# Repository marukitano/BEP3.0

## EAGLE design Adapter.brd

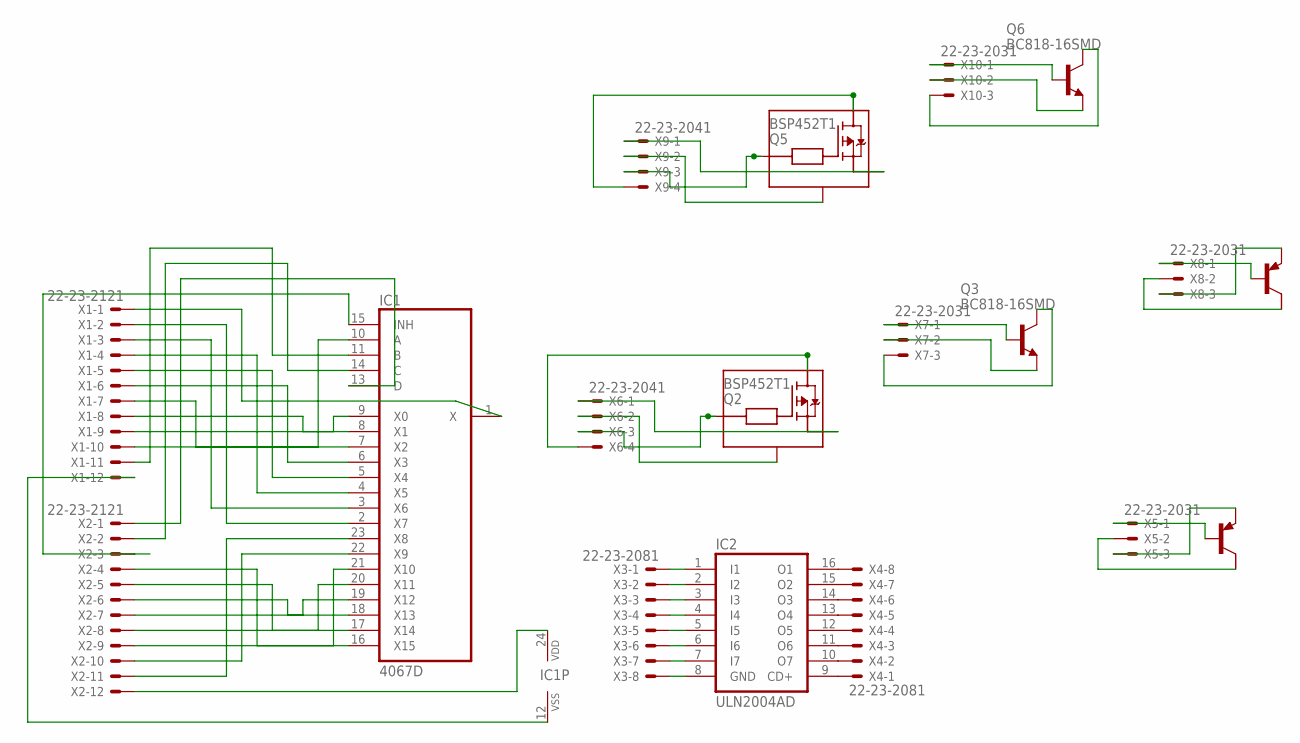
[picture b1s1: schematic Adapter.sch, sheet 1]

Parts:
IC1: 4067D; SO24W
IC2: ULN2004AD; SO16
Q1, Q4: BCP53T1; SOT223
Q2, Q5: BSP452T1; SOT223
Q3, Q6: BC818-16SMD; SOT23-BEC
X1, X2: 22-23-2121
X3, X4: 22-23-2081
X5, X7, X8, X10: 22-23-2031
X6, X9: 22-23-2041

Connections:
unnamed: IC1.2 (X7), X1.2
unnamed: IC1.1 (X), X1.1
unnamed: IC1.3 (X6), X1.3
unnamed: IC1.4 (X5), X1.4
unnamed: IC1.5 (X4), X1.5
unnamed: IC1.6 (X3), X1.6
unnamed: IC1.7 (X2), X1.7
unnamed: IC1.8 (X1), X1.8
unnamed: IC1.9 (X0), X1.9
unnamed: IC1.10 (A), X1.10
unnamed: IC1.11 (B), X1.11
unnamed: IC1.16 (X15), X2.4
unnamed: IC1.17 (X14), X2.5
unnamed: IC1.18 (X13), X2.6
unnamed: IC1.19 (X12), X2.7
unnamed: IC1.20 (X11), X2.8
unnamed: IC1.21 (X10), X2.9
unnamed: IC1.22 (X9), X2.10
unnamed: IC1.23 (X8), X2.11
unnamed: IC1.12 (VSS), X1.12
unnamed: IC1.24 (VDD), X2.12
unnamed: IC1.15 (INH), X2.3
unnamed: IC1.14 (C), X2.2
unnamed: IC1.13 (D), X2.1
unnamed: IC2.1 (I1), X3.1
unnamed: IC2.2 (I2), X3.2
unnamed: IC2.3 (I3), X3.3
unnamed: IC2.4 (I4), X3.4
unnamed: IC2.5 (I5), X3.5
unnamed: IC2.6 (I6), X3.6
unnamed: IC2.7 (I7), X3.7
unnamed: IC2.8 (GND), X3.8
unnamed: IC2.9 (CD+), X4.1
unnamed: IC2.10 (O7), X4.2
unnamed: IC2.11 (O6), X4.3
unnamed: IC2.12 (O5), X4.4
unnamed: IC2.13 (O4), X4.5
unnamed: IC2.14 (O3), X4.6
unnamed: IC2.15 (O2), X4.7
unnamed: IC2.16 (O1), X4.8
unnamed: Q1.1 (B), X5.1
unnamed: Q1.3 (E), X5.3
unnamed: Q1.2 (C), X5.2
unnamed: Q2.1 (OUT), X6.1
unnamed: Q2.2 (GND), X6.2
unnamed: Q2.3 (IN), X6.3
unnamed: Q2.4 (V+), X6.4
unnamed: Q3.B, X7.1
unnamed: Q3.E, X7.2
unnamed: Q3.C, X7.3
unnamed: Q4.1 (B), X8.1
unnamed: Q4.2 (C), X8.2
unnamed: Q4.3 (E), X8.3
unnamed: Q5.1 (OUT), X9.1
unnamed: Q5.2 (GND), X9.2
unnamed: Q5.3 (IN), X9.3
unnamed: Q5.4 (V+), X9.4
unnamed: Q6.B, X10.1
unnamed: Q6.E, X10.2
unnamed: Q6.C, X10.3

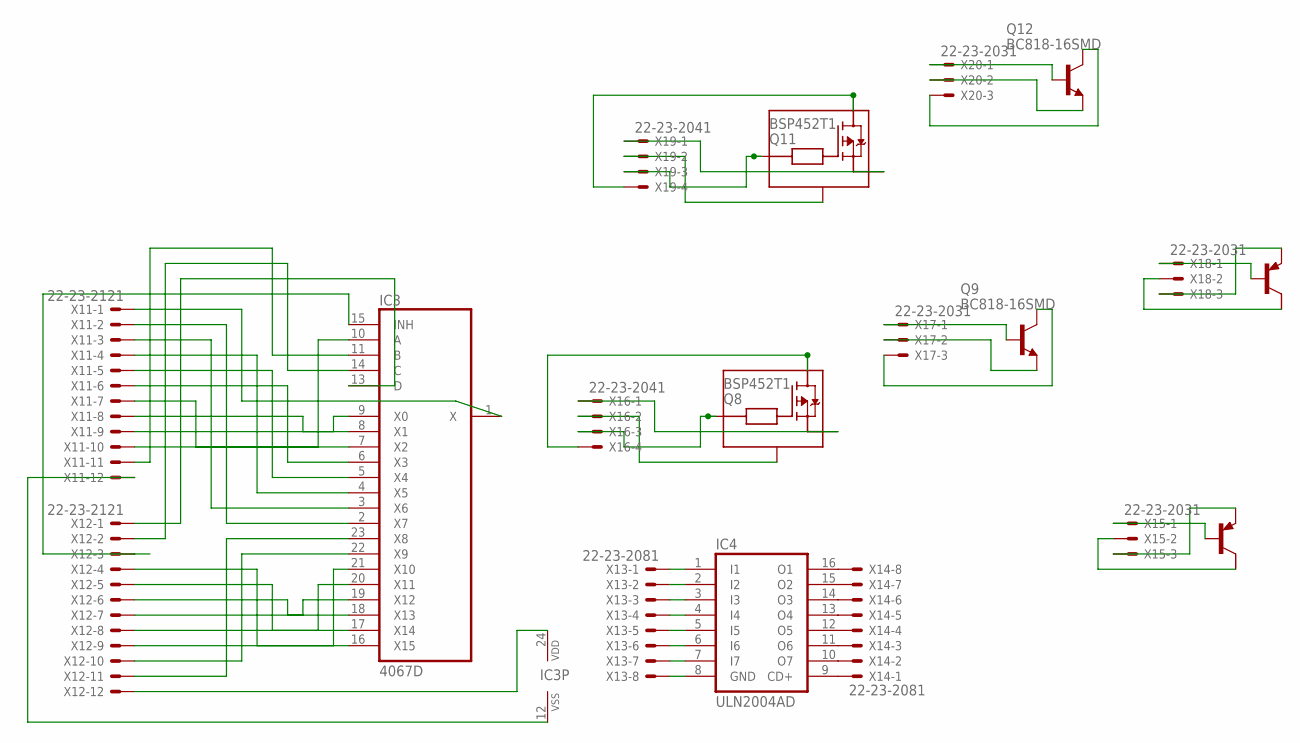
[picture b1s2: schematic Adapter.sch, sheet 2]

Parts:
IC3: 4067D; SO24W
IC4: ULN2004AD; SO16
Q7, Q10: BCP53T1; SOT223
Q8, Q11: BSP452T1; SOT223
Q9, Q12: BC818-16SMD; SOT23-BEC
X11, X12: 22-23-2121
X13, X14: 22-23-2081
X15, X17, X18, X20: 22-23-2031
X16, X19: 22-23-2041

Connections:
unnamed: IC3.2 (X7), X11.2
unnamed: IC3.1 (X), X11.1
unnamed: IC3.3 (X6), X11.3
unnamed: IC3.4 (X5), X11.4
unnamed: IC3.5 (X4), X11.5
unnamed: IC3.6 (X3), X11.6
unnamed: IC3.7 (X2), X11.7
unnamed: IC3.8 (X1), X11.8
unnamed: IC3.9 (X0), X11.9
unnamed: IC3.10 (A), X11.10
unnamed: IC3.11 (B), X11.11
unnamed: IC3.16 (X15), X12.4
unnamed: IC3.17 (X14), X12.5
unnamed: IC3.18 (X13), X12.6
unnamed: IC3.19 (X12), X12.7
unnamed: IC3.20 (X11), X12.8
unnamed: IC3.21 (X10), X12.9
unnamed: IC3.22 (X9), X12.10
unnamed: IC3.23 (X8), X12.11
unnamed: IC3.12 (VSS), X11.12
unnamed: IC3.24 (VDD), X12.12
unnamed: IC3.15 (INH), X12.3
unnamed: IC3.14 (C), X12.2
unnamed: IC3.13 (D), X12.1
unnamed: IC4.1 (I1), X13.1
unnamed: IC4.2 (I2), X13.2
unnamed: IC4.3 (I3), X13.3
unnamed: IC4.4 (I4), X13.4
unnamed: IC4.5 (I5), X13.5
unnamed: IC4.6 (I6), X13.6
unnamed: IC4.7 (I7), X13.7
unnamed: IC4.8 (GND), X13.8
unnamed: IC4.9 (CD+), X14.1
unnamed: IC4.10 (O7), X14.2
unnamed: IC4.11 (O6), X14.3
unnamed: IC4.12 (O5), X14.4
unnamed: IC4.13 (O4), X14.5
unnamed: IC4.14 (O3), X14.6
unnamed: IC4.15 (O2), X14.7
unnamed: IC4.16 (O1), X14.8
unnamed: Q7.1 (B), X15.1
unnamed: Q7.2 (C), X15.2
unnamed: Q7.3 (E), X15.3
unnamed: Q8.1 (OUT), X16.1
unnamed: Q8.2 (GND), X16.2
unnamed: Q8.3 (IN), X16.3
unnamed: Q8.4 (V+), X16.4
unnamed: Q9.B, X17.1
unnamed: Q9.E, X17.2
unnamed: Q9.C, X17.3
unnamed: Q10.1 (B), X18.1
unnamed: Q10.2 (C), X18.2
unnamed: Q10.3 (E), X18.3
unnamed: Q11.1 (OUT), X19.1
unnamed: Q11.2 (GND), X19.2
unnamed: Q11.3 (IN), X19.3
unnamed: Q11.4 (V+), X19.4
unnamed: Q12.B, X20.1
unnamed: Q12.E, X20.2
unnamed: Q12.C, X20.3

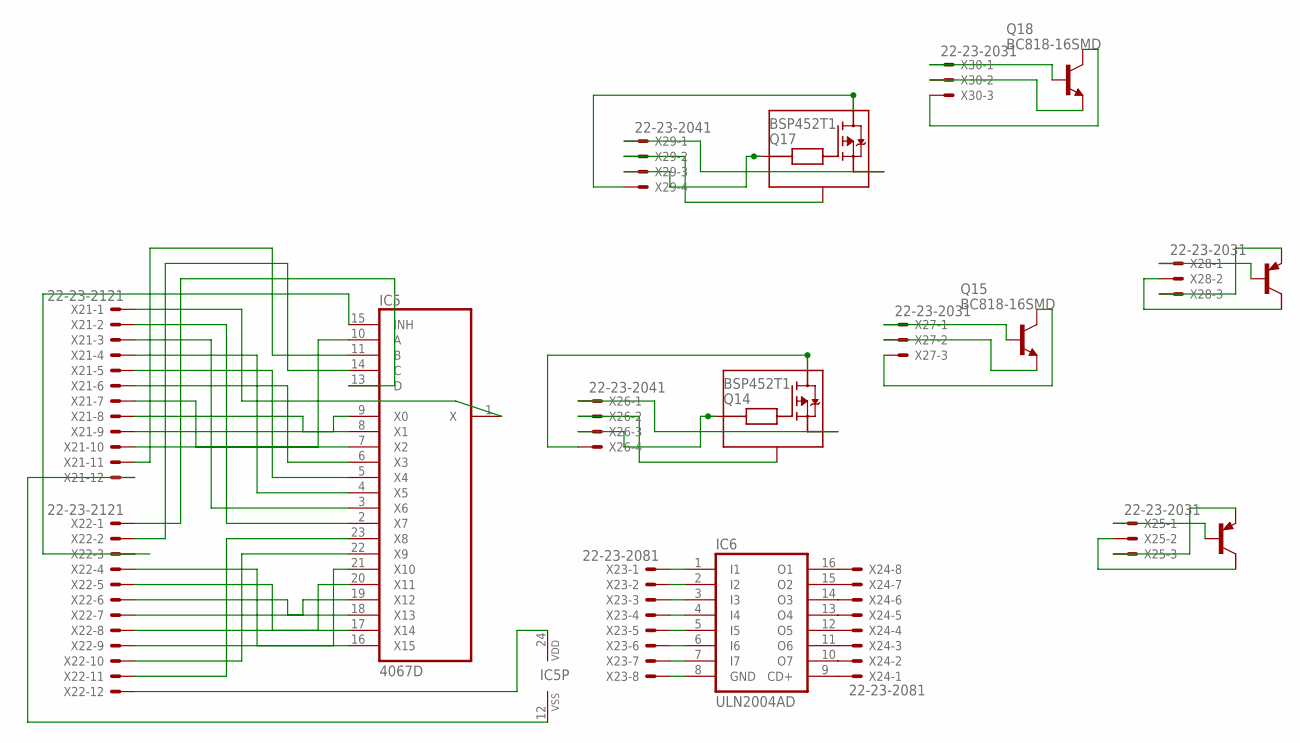
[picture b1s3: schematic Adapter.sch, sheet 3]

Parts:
IC5: 4067D; SO24W
IC6: ULN2004AD; SO16
Q13, Q16: BCP53T1; SOT223
Q14, Q17: BSP452T1; SOT223
Q15, Q18: BC818-16SMD; SOT23-BEC
X21, X22: 22-23-2121
X23, X24: 22-23-2081
X25, X27, X28, X30: 22-23-2031
X26, X29: 22-23-2041

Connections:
unnamed: IC5.2 (X7), X21.2
unnamed: IC5.1 (X), X21.1
unnamed: IC5.3 (X6), X21.3
unnamed: IC5.4 (X5), X21.4
unnamed: IC5.5 (X4), X21.5
unnamed: IC5.6 (X3), X21.6
unnamed: IC5.7 (X2), X21.7
unnamed: IC5.8 (X1), X21.8
unnamed: IC5.9 (X0), X21.9
unnamed: IC5.10 (A), X21.10
unnamed: IC5.11 (B), X21.11
unnamed: IC5.16 (X15), X22.4
unnamed: IC5.17 (X14), X22.5
unnamed: IC5.18 (X13), X22.6
unnamed: IC5.19 (X12), X22.7
unnamed: IC5.20 (X11), X22.8
unnamed: IC5.21 (X10), X22.9
unnamed: IC5.22 (X9), X22.10
unnamed: IC5.23 (X8), X22.11
unnamed: IC5.12 (VSS), X21.12
unnamed: IC5.24 (VDD), X22.12
unnamed: IC5.15 (INH), X22.3
unnamed: IC5.14 (C), X22.2
unnamed: IC5.13 (D), X22.1
unnamed: IC6.1 (I1), X23.1
unnamed: IC6.2 (I2), X23.2
unnamed: IC6.3 (I3), X23.3
unnamed: IC6.4 (I4), X23.4
unnamed: IC6.5 (I5), X23.5
unnamed: IC6.6 (I6), X23.6
unnamed: IC6.7 (I7), X23.7
unnamed: IC6.8 (GND), X23.8
unnamed: IC6.9 (CD+), X24.1
unnamed: IC6.10 (O7), X24.2
unnamed: IC6.11 (O6), X24.3
unnamed: IC6.12 (O5), X24.4
unnamed: IC6.13 (O4), X24.5
unnamed: IC6.14 (O3), X24.6
unnamed: IC6.15 (O2), X24.7
unnamed: IC6.16 (O1), X24.8
unnamed: Q13.1 (B), X25.1
unnamed: Q13.2 (C), X25.2
unnamed: Q13.3 (E), X25.3
unnamed: Q14.1 (OUT), X26.1
unnamed: Q14.2 (GND), X26.2
unnamed: Q14.3 (IN), X26.3
unnamed: Q14.4 (V+), X26.4
unnamed: Q15.B, X27.1
unnamed: Q15.E, X27.2
unnamed: Q15.C, X27.3
unnamed: Q16.1 (B), X28.1
unnamed: Q16.2 (C), X28.2
unnamed: Q16.3 (E), X28.3
unnamed: Q17.1 (OUT), X29.1
unnamed: Q17.2 (GND), X29.2
unnamed: Q17.3 (IN), X29.3
unnamed: Q17.4 (V+), X29.4
unnamed: Q18.B, X30.1
unnamed: Q18.E, X30.2
unnamed: Q18.C, X30.3

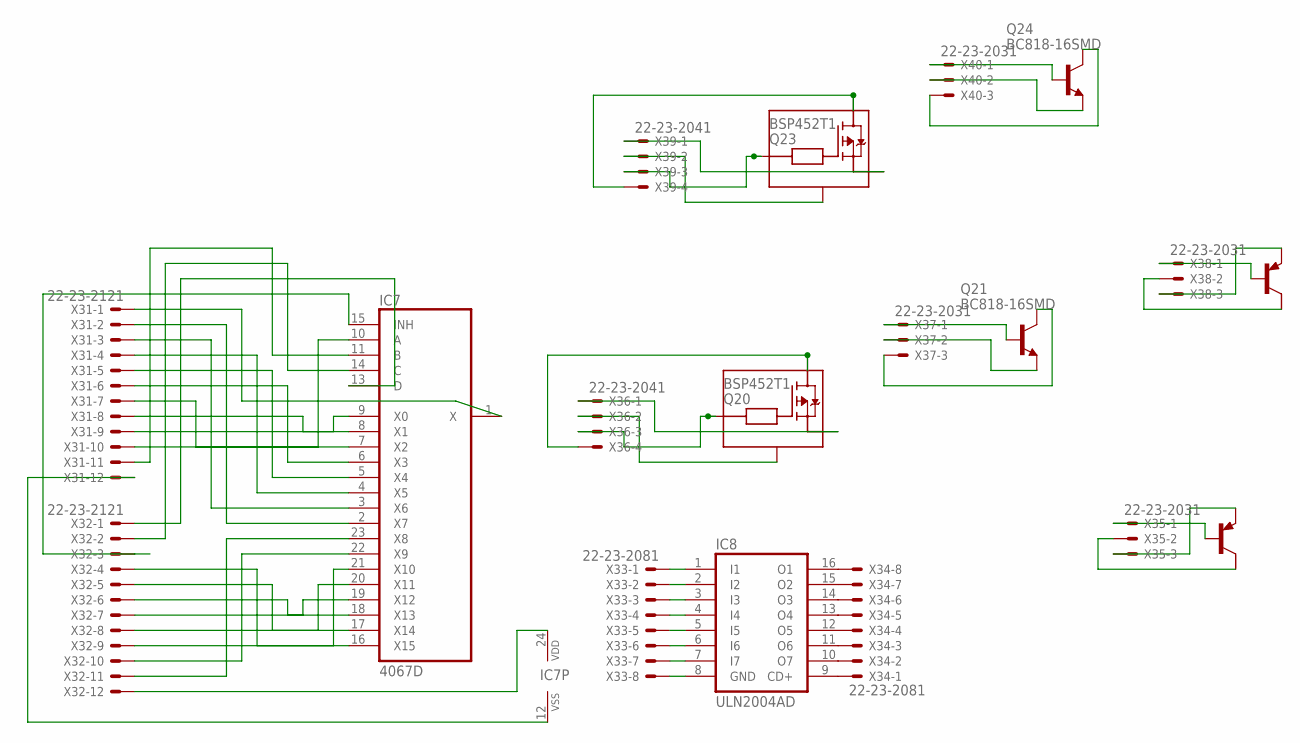
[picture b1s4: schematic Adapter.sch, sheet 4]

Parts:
IC7: 4067D; SO24W
IC8: ULN2004AD; SO16
Q19, Q22: BCP53T1; SOT223
Q20, Q23: BSP452T1; SOT223
Q21, Q24: BC818-16SMD; SOT23-BEC
X31, X32: 22-23-2121
X33, X34: 22-23-2081
X35, X37, X38, X40: 22-23-2031
X36, X39: 22-23-2041

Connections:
unnamed: IC7.2 (X7), X31.2
unnamed: IC7.1 (X), X31.1
unnamed: IC7.3 (X6), X31.3
unnamed: IC7.4 (X5), X31.4
unnamed: IC7.5 (X4), X31.5
unnamed: IC7.6 (X3), X31.6
unnamed: IC7.7 (X2), X31.7
unnamed: IC7.8 (X1), X31.8
unnamed: IC7.9 (X0), X31.9
unnamed: IC7.10 (A), X31.10
unnamed: IC7.11 (B), X31.11
unnamed: IC7.16 (X15), X32.4
unnamed: IC7.17 (X14), X32.5
unnamed: IC7.18 (X13), X32.6
unnamed: IC7.19 (X12), X32.7
unnamed: IC7.20 (X11), X32.8
unnamed: IC7.21 (X10), X32.9
unnamed: IC7.22 (X9), X32.10
unnamed: IC7.23 (X8), X32.11
unnamed: IC7.12 (VSS), X31.12
unnamed: IC7.24 (VDD), X32.12
unnamed: IC7.15 (INH), X32.3
unnamed: IC7.14 (C), X32.2
unnamed: IC7.13 (D), X32.1
unnamed: IC8.1 (I1), X33.1
unnamed: IC8.2 (I2), X33.2
unnamed: IC8.3 (I3), X33.3
unnamed: IC8.4 (I4), X33.4
unnamed: IC8.5 (I5), X33.5
unnamed: IC8.6 (I6), X33.6
unnamed: IC8.7 (I7), X33.7
unnamed: IC8.8 (GND), X33.8
unnamed: IC8.9 (CD+), X34.1
unnamed: IC8.10 (O7), X34.2
unnamed: IC8.11 (O6), X34.3
unnamed: IC8.12 (O5), X34.4
unnamed: IC8.13 (O4), X34.5
unnamed: IC8.14 (O3), X34.6
unnamed: IC8.15 (O2), X34.7
unnamed: IC8.16 (O1), X34.8
unnamed: Q19.1 (B), X35.1
unnamed: Q19.2 (C), X35.2
unnamed: Q19.3 (E), X35.3
unnamed: Q20.1 (OUT), X36.1
unnamed: Q20.2 (GND), X36.2
unnamed: Q20.3 (IN), X36.3
unnamed: Q20.4 (V+), X36.4
unnamed: Q21.B, X37.1
unnamed: Q21.E, X37.2
unnamed: Q21.C, X37.3
unnamed: Q22.1 (B), X38.1
unnamed: Q22.2 (C), X38.2
unnamed: Q22.3 (E), X38.3
unnamed: Q23.1 (OUT), X39.1
unnamed: Q23.2 (GND), X39.2
unnamed: Q23.3 (IN), X39.3
unnamed: Q23.4 (V+), X39.4
unnamed: Q24.B, X40.1
unnamed: Q24.E, X40.2
unnamed: Q24.C, X40.3

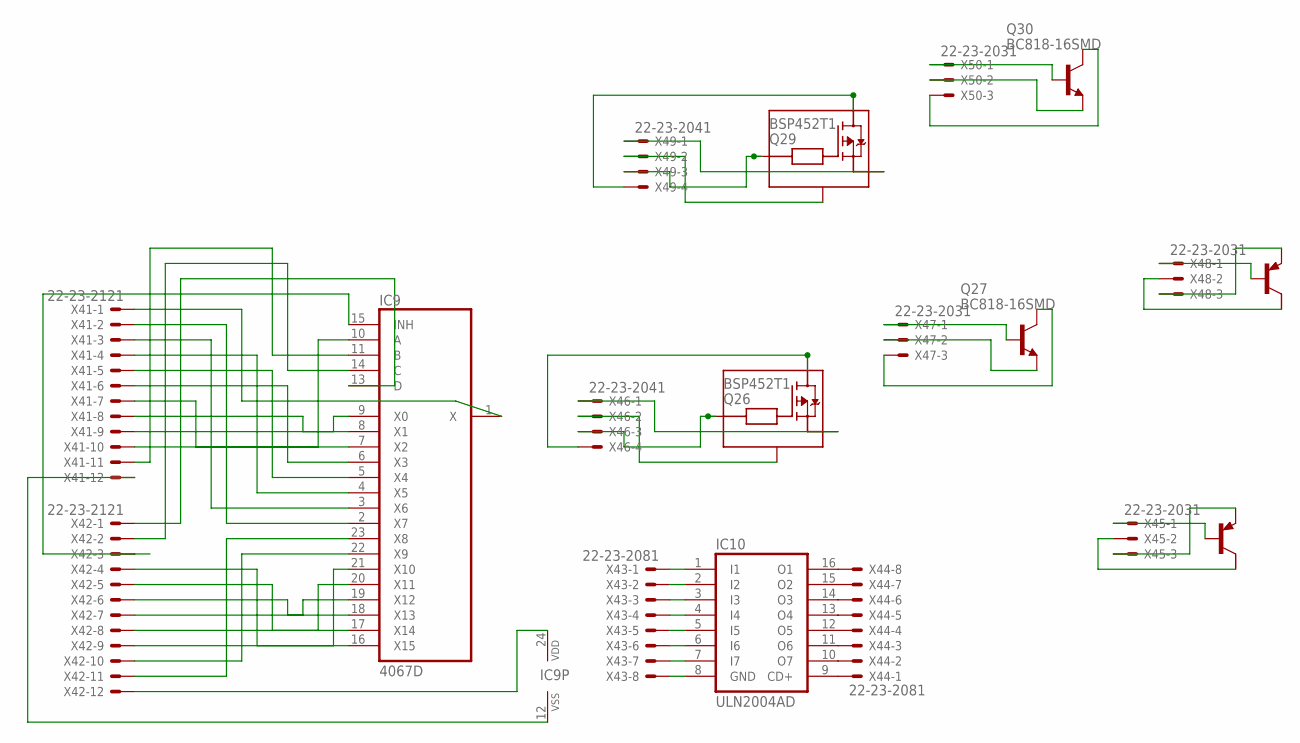
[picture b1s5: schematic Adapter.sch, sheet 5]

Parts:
IC9: 4067D; SO24W
IC10: ULN2004AD; SO16
Q25, Q28: BCP53T1; SOT223
Q26, Q29: BSP452T1; SOT223
Q27, Q30: BC818-16SMD; SOT23-BEC
X41, X42: 22-23-2121
X43, X44: 22-23-2081
X45, X47, X48, X50: 22-23-2031
X46, X49: 22-23-2041

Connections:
unnamed: IC9.2 (X7), X41.2
unnamed: IC9.1 (X), X41.1
unnamed: IC9.3 (X6), X41.3
unnamed: IC9.4 (X5), X41.4
unnamed: IC9.5 (X4), X41.5
unnamed: IC9.6 (X3), X41.6
unnamed: IC9.7 (X2), X41.7
unnamed: IC9.8 (X1), X41.8
unnamed: IC9.9 (X0), X41.9
unnamed: IC9.10 (A), X41.10
unnamed: IC9.11 (B), X41.11
unnamed: IC9.16 (X15), X42.4
unnamed: IC9.17 (X14), X42.5
unnamed: IC9.18 (X13), X42.6
unnamed: IC9.19 (X12), X42.7
unnamed: IC9.20 (X11), X42.8
unnamed: IC9.21 (X10), X42.9
unnamed: IC9.22 (X9), X42.10
unnamed: IC9.23 (X8), X42.11
unnamed: IC9.12 (VSS), X41.12
unnamed: IC9.24 (VDD), X42.12
unnamed: IC9.15 (INH), X42.3
unnamed: IC9.14 (C), X42.2
unnamed: IC9.13 (D), X42.1
unnamed: IC10.1 (I1), X43.1
unnamed: IC10.2 (I2), X43.2
unnamed: IC10.3 (I3), X43.3
unnamed: IC10.4 (I4), X43.4
unnamed: IC10.5 (I5), X43.5
unnamed: IC10.6 (I6), X43.6
unnamed: IC10.7 (I7), X43.7
unnamed: IC10.8 (GND), X43.8
unnamed: IC10.9 (CD+), X44.1
unnamed: IC10.10 (O7), X44.2
unnamed: IC10.11 (O6), X44.3
unnamed: IC10.12 (O5), X44.4
unnamed: IC10.13 (O4), X44.5
unnamed: IC10.14 (O3), X44.6
unnamed: IC10.15 (O2), X44.7
unnamed: IC10.16 (O1), X44.8
unnamed: Q25.1 (B), X45.1
unnamed: Q25.2 (C), X45.2
unnamed: Q25.3 (E), X45.3
unnamed: Q26.1 (OUT), X46.1
unnamed: Q26.2 (GND), X46.2
unnamed: Q26.3 (IN), X46.3
unnamed: Q26.4 (V+), X46.4
unnamed: Q27.B, X47.1
unnamed: Q27.E, X47.2
unnamed: Q27.C, X47.3
unnamed: Q28.1 (B), X48.1
unnamed: Q28.2 (C), X48.2
unnamed: Q28.3 (E), X48.3
unnamed: Q29.1 (OUT), X49.1
unnamed: Q29.2 (GND), X49.2
unnamed: Q29.3 (IN), X49.3
unnamed: Q29.4 (V+), X49.4
unnamed: Q30.B, X50.1
unnamed: Q30.E, X50.2
unnamed: Q30.C, X50.3

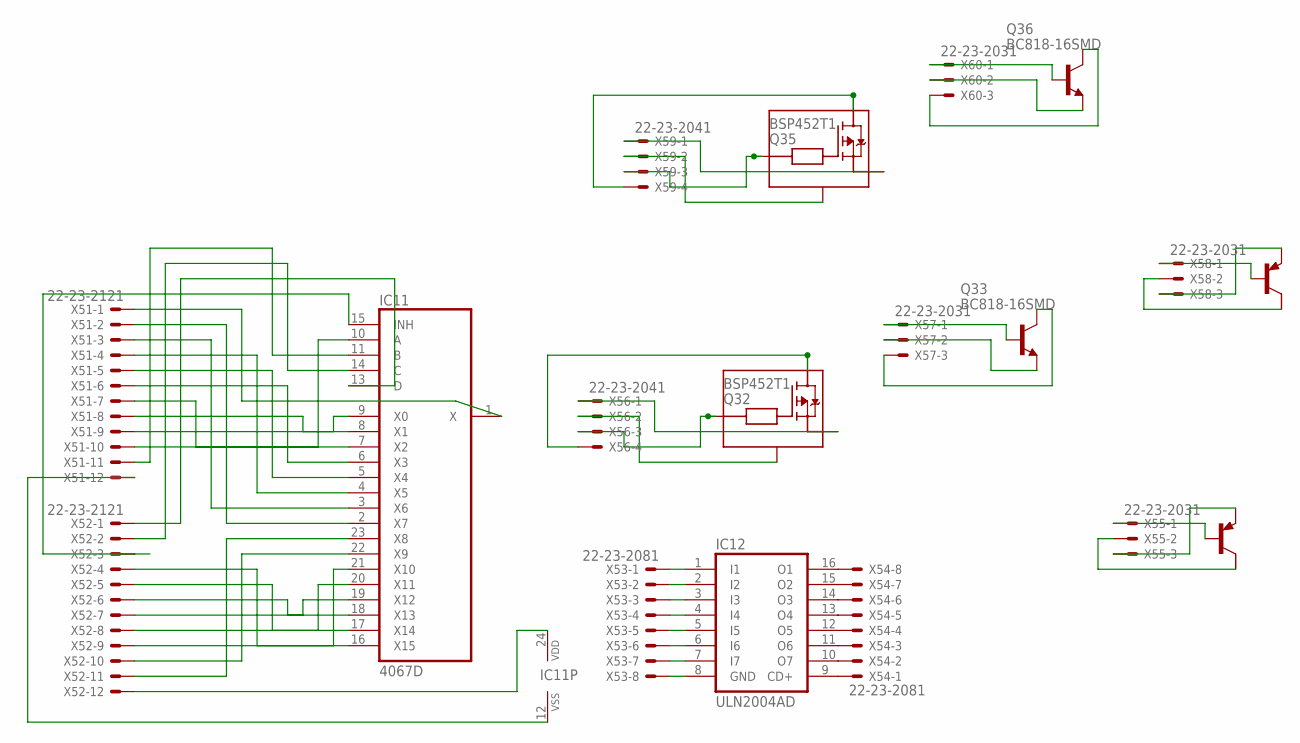
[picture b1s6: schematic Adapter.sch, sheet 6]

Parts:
IC11: 4067D; SO24W
IC12: ULN2004AD; SO16
Q31, Q34: BCP53T1; SOT223
Q32, Q35: BSP452T1; SOT223
Q33, Q36: BC818-16SMD; SOT23-BEC
X51, X52: 22-23-2121
X53, X54: 22-23-2081
X55, X57, X58, X60: 22-23-2031
X56, X59: 22-23-2041

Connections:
unnamed: IC11.2 (X7), X51.2
unnamed: IC11.1 (X), X51.1
unnamed: IC11.3 (X6), X51.3
unnamed: IC11.4 (X5), X51.4
unnamed: IC11.5 (X4), X51.5
unnamed: IC11.6 (X3), X51.6
unnamed: IC11.7 (X2), X51.7
unnamed: IC11.8 (X1), X51.8
unnamed: IC11.9 (X0), X51.9
unnamed: IC11.10 (A), X51.10
unnamed: IC11.11 (B), X51.11
unnamed: IC11.16 (X15), X52.4
unnamed: IC11.17 (X14), X52.5
unnamed: IC11.18 (X13), X52.6
unnamed: IC11.19 (X12), X52.7
unnamed: IC11.20 (X11), X52.8
unnamed: IC11.21 (X10), X52.9
unnamed: IC11.22 (X9), X52.10
unnamed: IC11.23 (X8), X52.11
unnamed: IC11.12 (VSS), X51.12
unnamed: IC11.24 (VDD), X52.12
unnamed: IC11.15 (INH), X52.3
unnamed: IC11.14 (C), X52.2
unnamed: IC11.13 (D), X52.1
unnamed: IC12.1 (I1), X53.1
unnamed: IC12.2 (I2), X53.2
unnamed: IC12.3 (I3), X53.3
unnamed: IC12.4 (I4), X53.4
unnamed: IC12.5 (I5), X53.5
unnamed: IC12.6 (I6), X53.6
unnamed: IC12.7 (I7), X53.7
unnamed: IC12.8 (GND), X53.8
unnamed: IC12.9 (CD+), X54.1
unnamed: IC12.10 (O7), X54.2
unnamed: IC12.11 (O6), X54.3
unnamed: IC12.12 (O5), X54.4
unnamed: IC12.13 (O4), X54.5
unnamed: IC12.14 (O3), X54.6
unnamed: IC12.15 (O2), X54.7
unnamed: IC12.16 (O1), X54.8
unnamed: Q31.1 (B), X55.1
unnamed: Q31.2 (C), X55.2
unnamed: Q31.3 (E), X55.3
unnamed: Q32.1 (OUT), X56.1
unnamed: Q32.2 (GND), X56.2
unnamed: Q32.3 (IN), X56.3
unnamed: Q32.4 (V+), X56.4
unnamed: Q33.B, X57.1
unnamed: Q33.E, X57.2
unnamed: Q33.C, X57.3
unnamed: Q34.1 (B), X58.1
unnamed: Q34.2 (C), X58.2
unnamed: Q34.3 (E), X58.3
unnamed: Q35.1 (OUT), X59.1
unnamed: Q35.2 (GND), X59.2
unnamed: Q35.3 (IN), X59.3
unnamed: Q35.4 (V+), X59.4
unnamed: Q36.B, X60.1
unnamed: Q36.E, X60.2
unnamed: Q36.C, X60.3

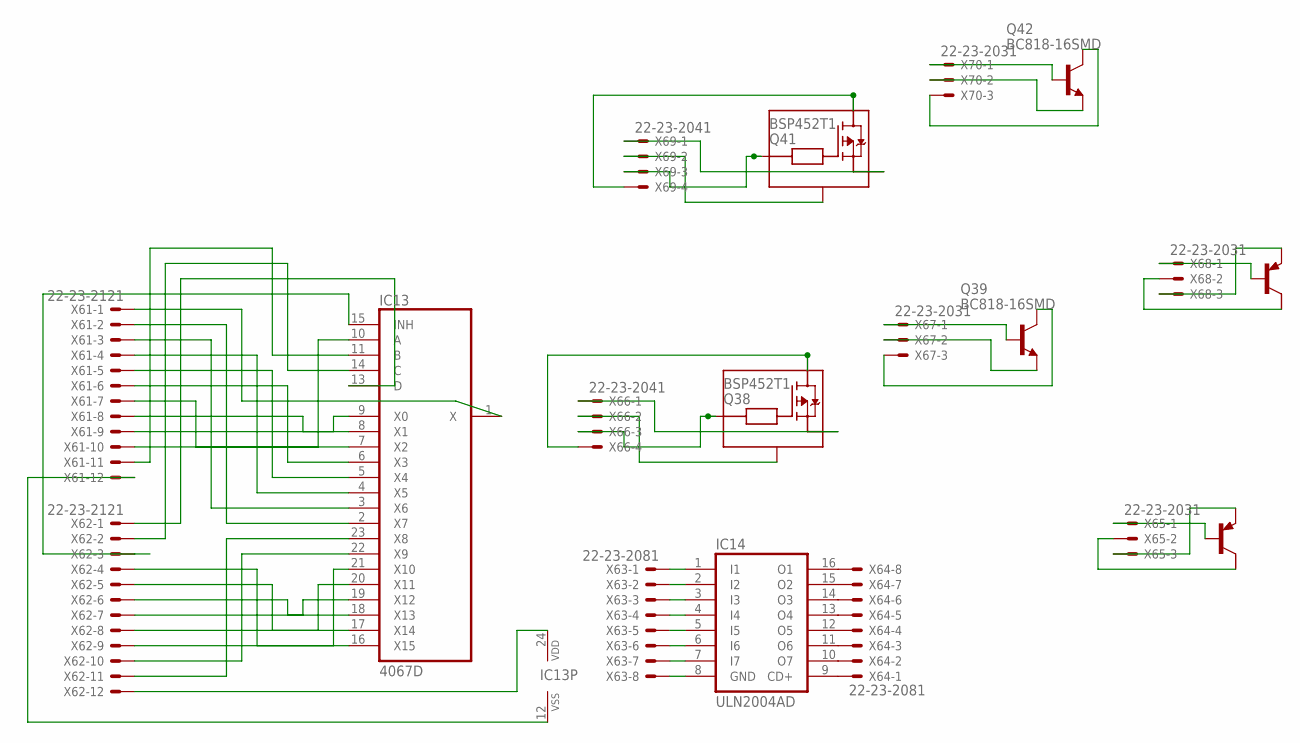
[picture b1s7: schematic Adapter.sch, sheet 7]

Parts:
IC13: 4067D; SO24W
IC14: ULN2004AD; SO16
Q37, Q40: BCP53T1; SOT223
Q38, Q41: BSP452T1; SOT223
Q39, Q42: BC818-16SMD; SOT23-BEC
X61, X62: 22-23-2121
X63, X64: 22-23-2081
X65, X67, X68, X70: 22-23-2031
X66, X69: 22-23-2041

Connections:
unnamed: IC13.2 (X7), X61.2
unnamed: IC13.1 (X), X61.1
unnamed: IC13.3 (X6), X61.3
unnamed: IC13.4 (X5), X61.4
unnamed: IC13.5 (X4), X61.5
unnamed: IC13.6 (X3), X61.6
unnamed: IC13.7 (X2), X61.7
unnamed: IC13.8 (X1), X61.8
unnamed: IC13.9 (X0), X61.9
unnamed: IC13.10 (A), X61.10
unnamed: IC13.11 (B), X61.11
unnamed: IC13.16 (X15), X62.4
unnamed: IC13.17 (X14), X62.5
unnamed: IC13.18 (X13), X62.6
unnamed: IC13.19 (X12), X62.7
unnamed: IC13.20 (X11), X62.8
unnamed: IC13.21 (X10), X62.9
unnamed: IC13.22 (X9), X62.10
unnamed: IC13.23 (X8), X62.11
unnamed: IC13.12 (VSS), X61.12
unnamed: IC13.24 (VDD), X62.12
unnamed: IC13.15 (INH), X62.3
unnamed: IC13.14 (C), X62.2
unnamed: IC13.13 (D), X62.1
unnamed: IC14.1 (I1), X63.1
unnamed: IC14.2 (I2), X63.2
unnamed: IC14.3 (I3), X63.3
unnamed: IC14.4 (I4), X63.4
unnamed: IC14.5 (I5), X63.5
unnamed: IC14.6 (I6), X63.6
unnamed: IC14.7 (I7), X63.7
unnamed: IC14.8 (GND), X63.8
unnamed: IC14.9 (CD+), X64.1
unnamed: IC14.10 (O7), X64.2
unnamed: IC14.11 (O6), X64.3
unnamed: IC14.12 (O5), X64.4
unnamed: IC14.13 (O4), X64.5
unnamed: IC14.14 (O3), X64.6
unnamed: IC14.15 (O2), X64.7
unnamed: IC14.16 (O1), X64.8
unnamed: Q37.1 (B), X65.1
unnamed: Q37.2 (C), X65.2
unnamed: Q37.3 (E), X65.3
unnamed: Q38.1 (OUT), X66.1
unnamed: Q38.2 (GND), X66.2
unnamed: Q38.3 (IN), X66.3
unnamed: Q38.4 (V+), X66.4
unnamed: Q39.B, X67.1
unnamed: Q39.E, X67.2
unnamed: Q39.C, X67.3
unnamed: Q40.1 (B), X68.1
unnamed: Q40.2 (C), X68.2
unnamed: Q40.3 (E), X68.3
unnamed: Q41.1 (OUT), X69.1
unnamed: Q41.2 (GND), X69.2
unnamed: Q41.3 (IN), X69.3
unnamed: Q41.4 (V+), X69.4
unnamed: Q42.B, X70.1
unnamed: Q42.E, X70.2
unnamed: Q42.C, X70.3

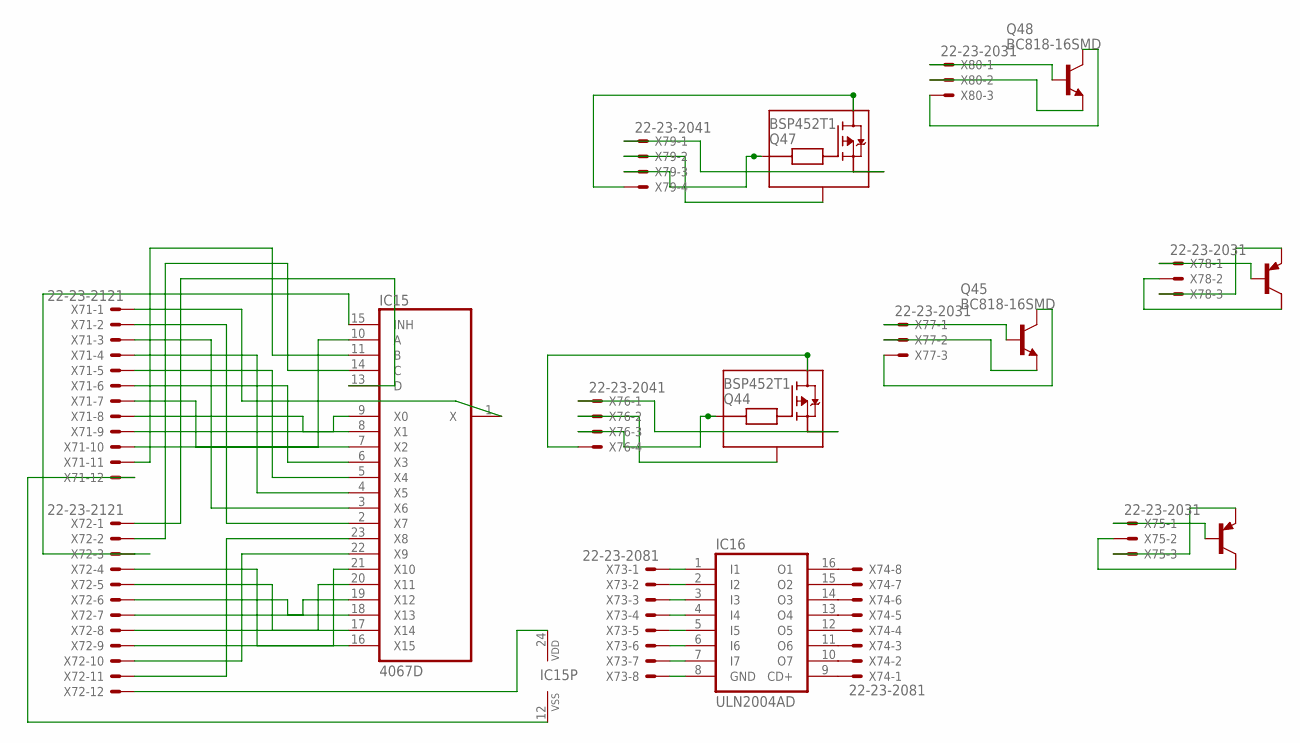
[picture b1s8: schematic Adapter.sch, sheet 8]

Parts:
IC15: 4067D; SO24W
IC16: ULN2004AD; SO16
Q43, Q46: BCP53T1; SOT223
Q44, Q47: BSP452T1; SOT223
Q45, Q48: BC818-16SMD; SOT23-BEC
X71, X72: 22-23-2121
X73, X74: 22-23-2081
X75, X77, X78, X80: 22-23-2031
X76, X79: 22-23-2041

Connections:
unnamed: IC15.2 (X7), X71.2
unnamed: IC15.1 (X), X71.1
unnamed: IC15.3 (X6), X71.3
unnamed: IC15.4 (X5), X71.4
unnamed: IC15.5 (X4), X71.5
unnamed: IC15.6 (X3), X71.6
unnamed: IC15.7 (X2), X71.7
unnamed: IC15.8 (X1), X71.8
unnamed: IC15.9 (X0), X71.9
unnamed: IC15.10 (A), X71.10
unnamed: IC15.11 (B), X71.11
unnamed: IC15.16 (X15), X72.4
unnamed: IC15.17 (X14), X72.5
unnamed: IC15.18 (X13), X72.6
unnamed: IC15.19 (X12), X72.7
unnamed: IC15.20 (X11), X72.8
unnamed: IC15.21 (X10), X72.9
unnamed: IC15.22 (X9), X72.10
unnamed: IC15.23 (X8), X72.11
unnamed: IC15.12 (VSS), X71.12
unnamed: IC15.24 (VDD), X72.12
unnamed: IC15.15 (INH), X72.3
unnamed: IC15.14 (C), X72.2
unnamed: IC15.13 (D), X72.1
unnamed: IC16.1 (I1), X73.1
unnamed: IC16.2 (I2), X73.2
unnamed: IC16.3 (I3), X73.3
unnamed: IC16.4 (I4), X73.4
unnamed: IC16.5 (I5), X73.5
unnamed: IC16.6 (I6), X73.6
unnamed: IC16.7 (I7), X73.7
unnamed: IC16.8 (GND), X73.8
unnamed: IC16.9 (CD+), X74.1
unnamed: IC16.10 (O7), X74.2
unnamed: IC16.11 (O6), X74.3
unnamed: IC16.12 (O5), X74.4
unnamed: IC16.13 (O4), X74.5
unnamed: IC16.14 (O3), X74.6
unnamed: IC16.15 (O2), X74.7
unnamed: IC16.16 (O1), X74.8
unnamed: Q43.1 (B), X75.1
unnamed: Q43.2 (C), X75.2
unnamed: Q43.3 (E), X75.3
unnamed: Q44.1 (OUT), X76.1
unnamed: Q44.2 (GND), X76.2
unnamed: Q44.3 (IN), X76.3
unnamed: Q44.4 (V+), X76.4
unnamed: Q45.B, X77.1
unnamed: Q45.E, X77.2
unnamed: Q45.C, X77.3
unnamed: Q46.1 (B), X78.1
unnamed: Q46.2 (C), X78.2
unnamed: Q46.3 (E), X78.3
unnamed: Q47.1 (OUT), X79.1
unnamed: Q47.2 (GND), X79.2
unnamed: Q47.3 (IN), X79.3
unnamed: Q47.4 (V+), X79.4
unnamed: Q48.B, X80.1
unnamed: Q48.E, X80.2
unnamed: Q48.C, X80.3

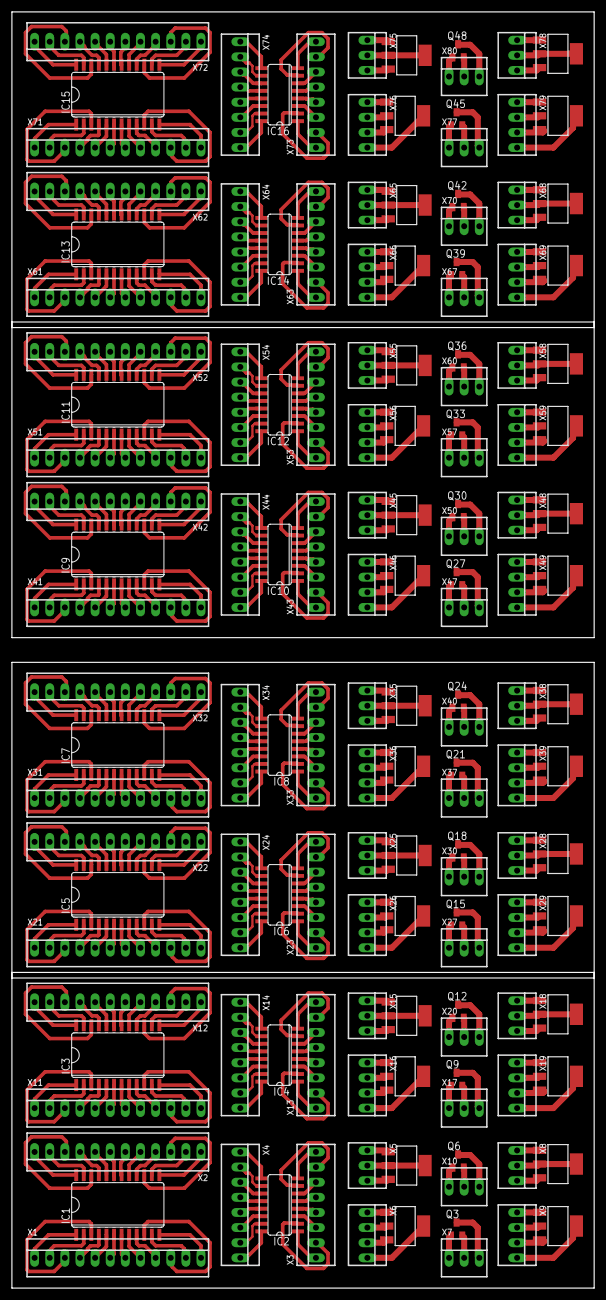
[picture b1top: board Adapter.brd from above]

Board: 2 copper layers, 97.8 x 214.3 mm, 144 parts (0 on the bottom side), 480 nets.

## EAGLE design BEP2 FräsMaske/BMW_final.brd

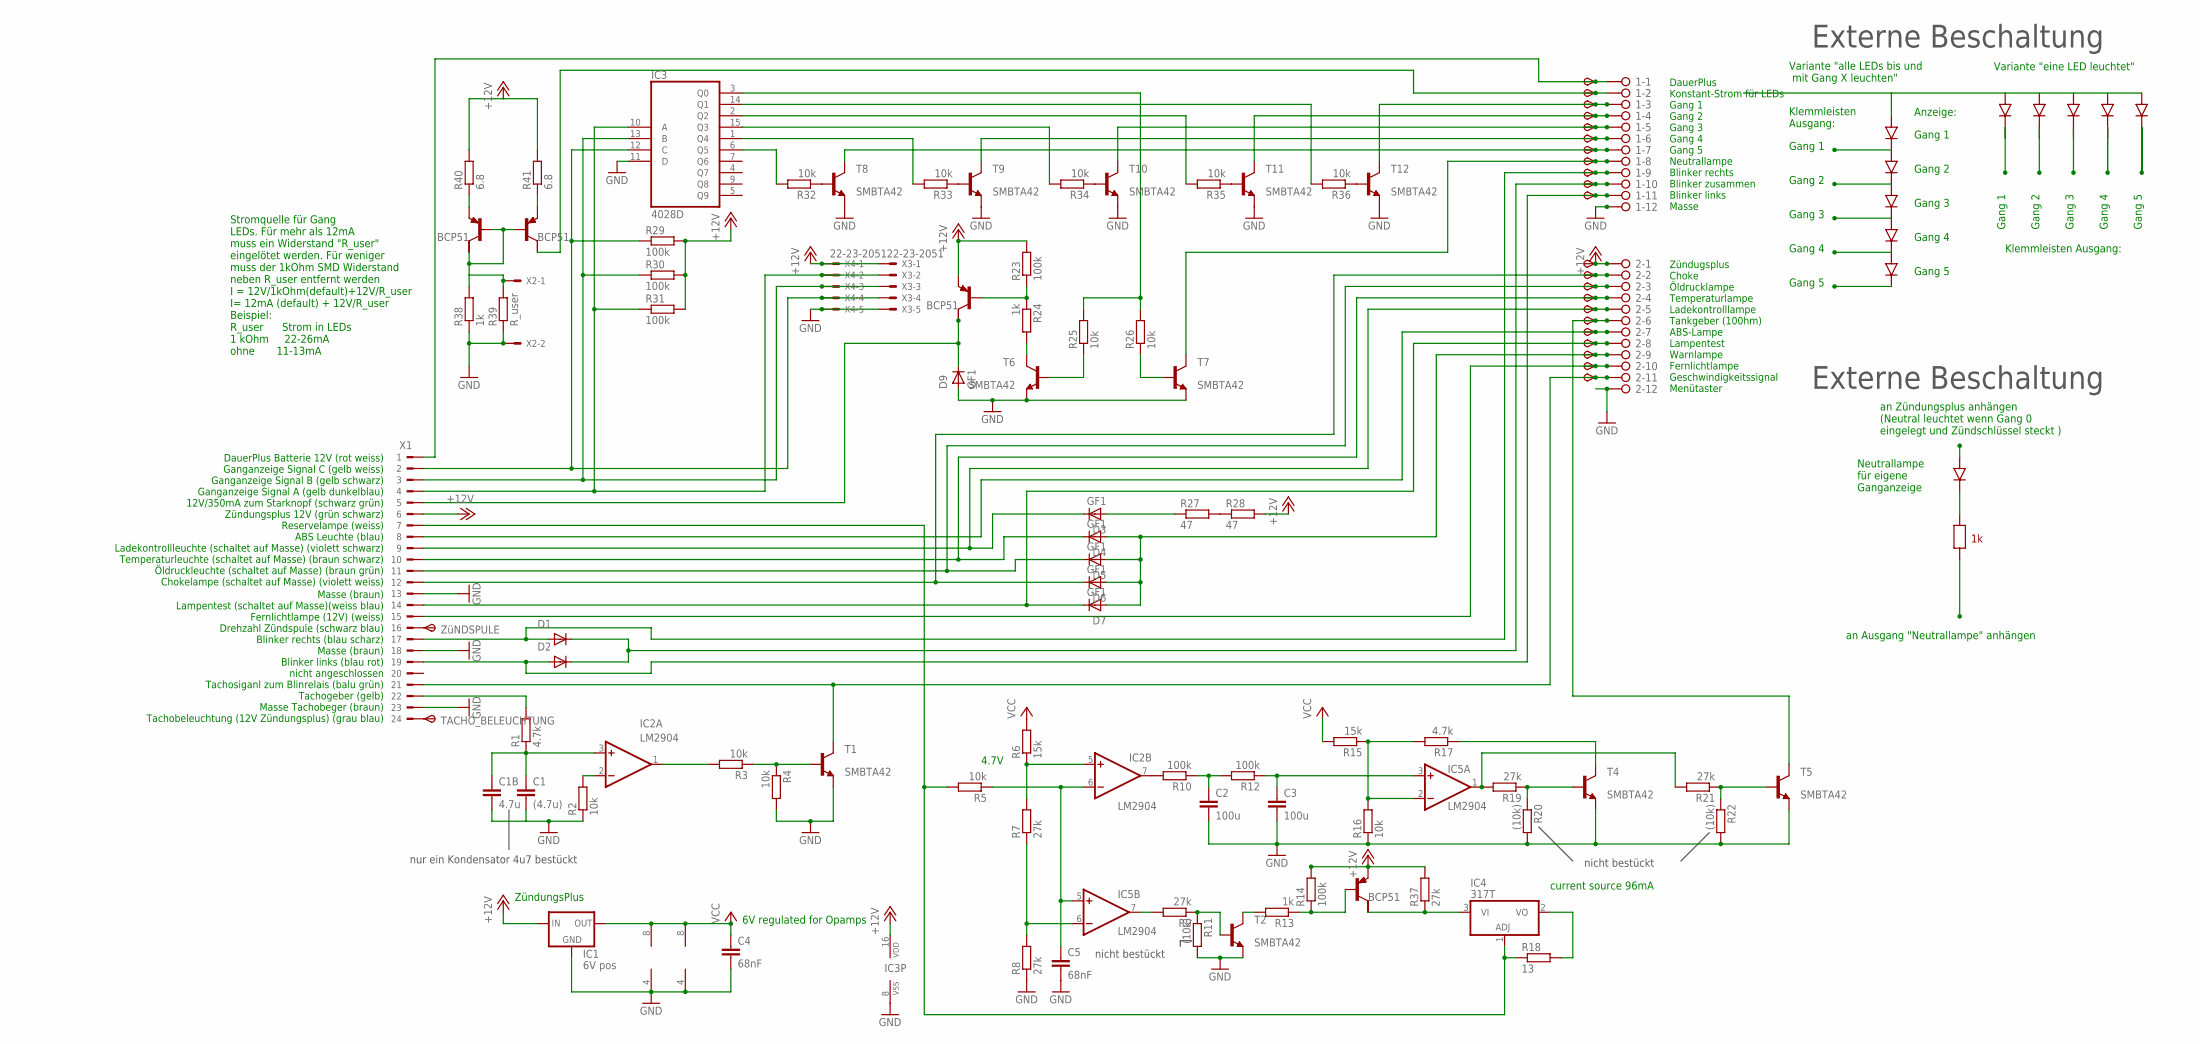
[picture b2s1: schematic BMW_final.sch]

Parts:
1, 2: 2081-1132; 12-PIN
C1: (4.7u); C1206
C1B: 4.7u; C0805K
C2, C3: 100u; C1206K
C4, C5: 68nF; C1206K
D1, D2, D3, D4, D5, D6, D7, D9: GF1; SMA-DO214AC
IC1: 6V pos; 78LXX
IC2, IC5: LM2904; SO08
IC3: 4028D; SO16
IC4: 317T; TO220H
R1, R17: 4.7k; R0805
R2, R3, R4, R5, R16, R25, R26, R32, R33, R34, R35, R36: 10k; R0805
R6, R15: 15k; R0805
R7, R8, R9, R19, R21, R37: 27k; R0805
R10, R12, R14, R23, R29, R30, R31: 100k; R0805
R11, R20, R22: (10k); R0805
R13, R24, R38: 1k; R0805
R18: 13; 0207/10
R27, R28: 47; V235/17
R39: R_user; R0805
R40, R41: 6.8; R0805
T, T3, T13, T14: BCP53T1; SOT223
T1, T2, T4, T5, T6, T7, T8, T9, T10, T11, T12: MMBTA42LT1-NPN-SOT23-BEC; SOT23-BEC
TACHO_BELEUCHTUNG: TPSP1_1MM; P1_1.0MM
TP1, TP2, TP3, TP4, TP5, TP6, TP7, TP8, TP9, TP10, TP11, TP12, TP16, TP17, TP18, TP19, TP21, TP22, TP23, TP24, TP25, TP26: TPSB1,27; B1,27
X1: CON_BMW; 24-PIN
X2: 22-23-2021
X3, X4: 22-23-2051
ZüNDSPULE: TPSP1_1MM; P1_1.0MM

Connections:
+12V: 2.1, IC1.IN, IC3.16 (VDD), R14.2, R23.2, R28.2, R29.2, R30.2, R31.2, R37.2, R40.2, R41.2, T.3 (E), T3.3 (E), TP12.TP, X1.6, X3.1, X4.1
GND: 1.12, 2.12, C1.2, C1B.2, C2.2, C3.2, C4.2, C5.2, D9.A, IC1.GND, IC2.4 (V-), IC3.8 (VSS), IC3.11 (D), IC5.4 (V-), R2.1, R4.2, R8.1, R11.2, R16.1, R20.2, R22.2, R38.1, R39.1, T1.E, T2.E, T4.E, T5.E, T6.E, T7.E, T8.E, T9.E, T10.E, T11.E, T12.E, X1.13, X1.18, X1.23, X2.2, X3.5, X4.5
unnamed: 2.9, D4.A, D5.A, D6.A, D7.A, TP24.TP
unnamed: IC3.10 (A), R31.1, X1.4, X3.2, X4.2
unnamed: IC3.13 (B), R30.1, X1.3, X3.3, X4.3
unnamed: 2.7, TP22.TP, X1.8
unnamed: R25.1, T6.B
unnamed: IC3.3 (Q0), R25.2, R26.2
unnamed: R24.2, T6.C
unnamed: R27.2, R28.1
unnamed: R23.1, R24.1, T.1 (B)
unnamed: R26.1, T7.B
unnamed: D9.K (C), T.2 (C), X1.5
unnamed: 2.2, D6.K (C), TP16.TP, X1.12
unnamed: 2.3, D5.K (C), TP17.TP, X1.11
unnamed: 2.4, D4.K (C), TP18.TP, X1.10
unnamed: IC4.1 (ADJ), R5.2, R18.1, X1.7
unnamed: C5.1, IC2.6 (-IN), IC5.5 (+IN), R5.1
unnamed: IC3.12 (C), R29.1, X1.2, X3.4, X4.4
unnamed: R32.1, T8.B
unnamed: 2.8, D7.K (C), TP23.TP, X1.14
unnamed: 1.9, D1.A, TP9.TP, X1.17
unnamed: 1.11, D2.A, TP11.TP, X1.19
unnamed: 1.10, D1.K (C), D2.K (C), TP10.TP
unnamed: R1.2, X1.22
unnamed: C1.1, C1B.1, IC2.3 (+IN), R1.1
unnamed: IC2.2 (-IN), R2.2
unnamed: 2.11, T1.C, TP26.TP, X1.21
unnamed: IC2.1 (OUT), R3.2
unnamed: R3.1, R4.1, T1.B
unnamed: IC4.2 (VO), R18.2
unnamed: IC5.6 (-IN), R7.1, R8.2
unnamed: IC5.7 (OUT), R9.2
unnamed: R13.2, T2.C
unnamed: R9.1, R11.1, T2.B
unnamed: IC4.3 (VI), R37.1, T3.2 (C)
unnamed: R13.1, R14.1, T3.1 (B)
unnamed: IC3.14 (Q1), R36.2
unnamed: IC3.2 (Q2), R35.2
unnamed: 1.5, T10.C, TP5.TP
unnamed: IC2.5 (+IN), R6.1, R7.2
unnamed: IC2.7 (OUT), R10.2
unnamed: X1.16, ZüNDSPULE.TP
unnamed: IC5.1 (OUT), R19.2, R21.2
unnamed: R19.1, R20.1, T4.B
unnamed: C2.1, R10.1, R12.2
unnamed: C3.1, IC5.3 (+IN), R12.1
unnamed: IC5.2 (-IN), R15.1, R16.2, R17.2
unnamed: R21.1, R22.1, T5.B
unnamed: R17.1, T4.C
unnamed: 1.6, T9.C, TP6.TP
unnamed: R34.1, T10.B
unnamed: 1.8, T7.C, TP8.TP
unnamed: 2.10, TP25.TP, X1.15
unnamed: D3.A, R27.1
unnamed: 2.5, D3.K (C), TP19.TP, X1.9
unnamed: R33.1, T9.B
unnamed: R35.1, T11.B
unnamed: TACHO_BELEUCHTUNG.TP, X1.24
unnamed: 1.2, T14.2 (C), TP2.TP
unnamed: 2.6, T5.C, TP21.TP
unnamed: IC3.6 (Q5), R32.2
unnamed: R36.1, T12.B
unnamed: 1.7, T8.C, TP7.TP
unnamed: IC3.1 (Q4), R33.2
unnamed: IC3.15 (Q3), R34.2
unnamed: 1.4, T11.C, TP4.TP
unnamed: 1.3, T12.C, TP3.TP
unnamed: R38.2, R39.2, T13.1 (B), T13.2 (C), T14.1 (B), X2.1
unnamed: 1.1, TP1.TP, X1.1
unnamed: R40.1, T13.3 (E)
unnamed: R41.1, T14.3 (E)
VCC: C4.1, IC1.OUT, IC2.8 (V+), IC5.8 (V+), R6.2, R15.2

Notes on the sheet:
6V regulated for Opamps
current source 96mA
ZündungsPlus
Zündugsplus Choke Öldrucklampe Temperaturlampe Ladekontrolllampe Tankgeber (100hm) ABS-Lampe Lampentest Warnlampe Fernlichtlampe Geschwindigkeitssignal Menütaster
DauerPlus Konstant-Strom für LEDs Gang 1 Gang 2 Gang 3 Gang 4 Gang 5 Neutrallampe Blinker rechts Blinker zusammen Blinker links Masse
DauerPlus Batterie 12V (rot weiss) Ganganzeige Signal C (gelb weiss) Ganganzeige Signal B (gelb schwarz) Ganganzeige Signal A (gelb dunkelblau) 12V/350mA zum Starknopf (schwarz grün) Zündungsplus 12V (grün schwarz) Reservelampe (weiss) ABS Leuchte (blau) Ladekontrollleuchte (schaltet auf Masse) (vi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
Masse (braun) Lampentest (schaltet auf Masse)(weiss blau) Fernlichtlampe (12V) (weiss) Drehzahl Zündspule (schwarz blau) Blinker rechts (blau scharz) Masse (braun) Blinker links (blau rot) nicht angeschlossen Tachosiganl zum Blinrelais (balu grün) Tachogeber (gelb) Masse Tachobeger (braun) Tachobel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
4.7V
Stromquelle für Gang LEDs. Für mehr als 12mA muss ein Widerstand "R_user" eingelötet werden. Für weniger muss der 1kOhm SMD Widerstand neben R_user entfernt werden I = 12V/1kOhm(default)+12V/R_user I= 12mA (default) + 12V/R_user Beispiel: R_user Strom in LEDs 1 kOhm 22-26mA ohne 11-13mA
Gang 1
Gang 2
Gang 3
Gang 4
Gang 5
Variante "eine LED leuchtet"
Variante "alle LEDs bis und mit Gang X leuchten"
Klemmleisten Ausgang:
Klemmleisten Ausgang:
an Zündungsplus anhängen (Neutral leuchtet wenn Gang 0 eingelegt und Zündschlüssel steckt )
an Ausgang "Neutrallampe" anhängen
Neutrallampe für eigene Ganganzeige
Externe Beschaltung
Anzeige:
nicht bestückt
nur ein Kondensator 4u7 bestückt
